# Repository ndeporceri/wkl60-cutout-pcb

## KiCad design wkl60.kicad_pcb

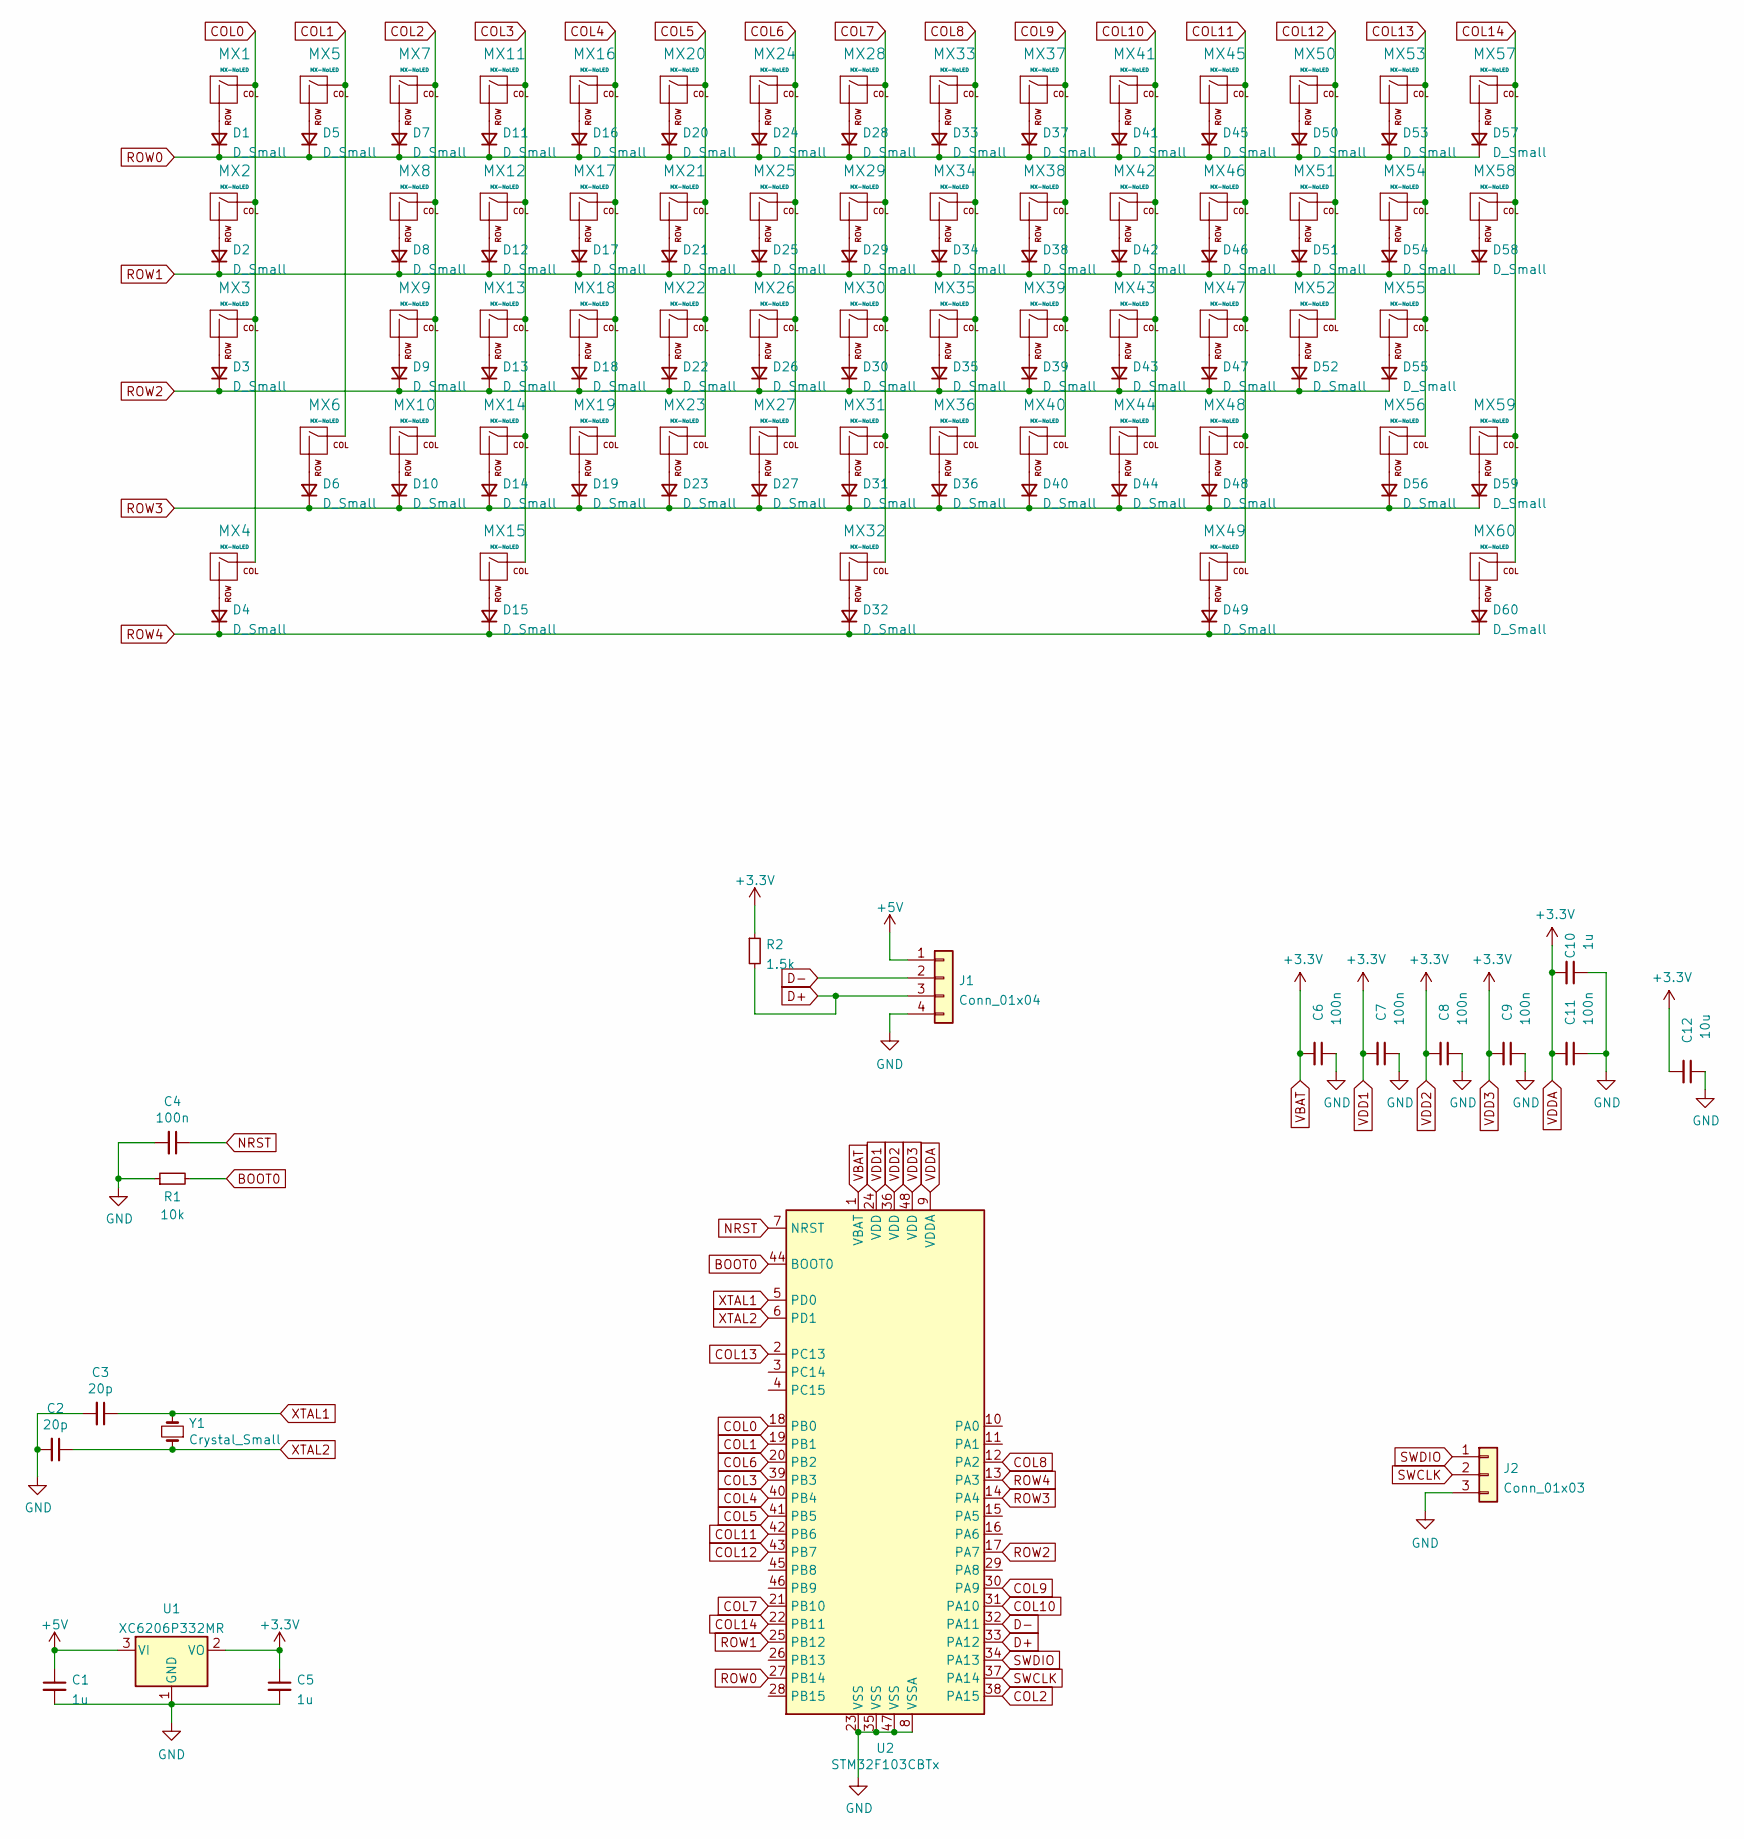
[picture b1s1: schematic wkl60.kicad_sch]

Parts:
C1, C5, C10: 1u; C_0603_1608Metric_Pad1.08x0.95mm_HandSolder
C2, C3: 20p; C_0603_1608Metric_Pad1.08x0.95mm_HandSolder
C4, C6, C7, C8, C9, C11: 100n; C_0603_1608Metric_Pad1.08x0.95mm_HandSolder
C12: 10u; C_0603_1608Metric_Pad1.08x0.95mm_HandSolder
D1, D2, D3, D4, D5, D6, D7, D8, D9, D10, D11, D12, D13, D14, D15, D16, D17, D18, D19, D20, D21, D22, D23, D24, D25, D26, D27, D28, D29, D30, D31, D32, D33, D34, D35, D36, D37, D38, D39, D40, D41, D42, D43, D44, D45, D46, D47, D48, D49, D50, D51, D52, D53, D54, D55, D56, D57, D58, D59, D60: D_Small; D_SOD-123F
J1: Conn_01x04; JST_SH_SM04B-SRSS-TB_1x04-1MP_P1.00mm_Horizontal
J2: Conn_01x03; PinHeader_1x03_P2.54mm_Vertical
MX1, MX5, MX7, MX8, MX9, MX10, MX11, MX12, MX13, MX14, MX16, MX17, MX18, MX19, MX20, MX21, MX22, MX23, MX24, MX25, MX26, MX27, MX28, MX29, MX30, MX31, MX33, MX34, MX35, MX36, MX37, MX38, MX39, MX40, MX41, MX42, MX43, MX44, MX45, MX46, MX47, MX48, MX50, MX51, MX52, MX53, MX54, MX57, MX59: MX-NoLED; MXOnly-1U-NoLED
MX2, MX4, MX15, MX49, MX58, MX60: MX-NoLED; MXOnly-1.5U-NoLED
MX3, MX56: MX-NoLED; MXOnly-1.75U-NoLED
MX6: MX-NoLED; MXOnly-2.25U-ReversedStabilizers-NoLED
MX32: MX-NoLED; MXOnly-7U-ReversedStabilizers-NoLED
MX55: MX-NoLED; MXOnly-2.25U-NoLED
R1: 10k; R_0603_1608Metric_Pad0.98x0.95mm_HandSolder
R2: 1.5k; R_0603_1608Metric_Pad0.98x0.95mm_HandSolder
U1: XC6206P332MR; SOT-23
U2: STM32F103CBTx; LQFP-48_7x7mm_P0.5mm; LCSC C77979
Y1: Crystal_Small; Crystal_SMD_5032-2Pin_5.0x3.2mm; LCSC C115962

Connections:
+5V: C1.1, J1.1, U1.3 (VI)
BOOT0: R1.2, U2.44 (BOOT0)
COL0: MX1.1 (COL), MX2.1 (COL), MX3.1 (COL), MX4.1 (COL), U2.18 (PB0)
COL1: MX5.1 (COL), MX6.1 (COL), U2.19 (PB1)
COL2: MX7.1 (COL), MX8.1 (COL), MX9.1 (COL), MX10.1 (COL), U2.38 (PA15)
COL3: MX11.1 (COL), MX12.1 (COL), MX13.1 (COL), MX14.1 (COL), MX15.1 (COL), U2.39 (PB3)
COL4: MX16.1 (COL), MX17.1 (COL), MX18.1 (COL), MX19.1 (COL), U2.40 (PB4)
COL5: MX20.1 (COL), MX21.1 (COL), MX22.1 (COL), MX23.1 (COL), U2.41 (PB5)
COL6: MX24.1 (COL), MX25.1 (COL), MX26.1 (COL), MX27.1 (COL), U2.20 (PB2)
COL7: MX28.1 (COL), MX29.1 (COL), MX30.1 (COL), MX31.1 (COL), MX32.1 (COL), U2.21 (PB10)
COL8: MX33.1 (COL), MX34.1 (COL), MX35.1 (COL), MX36.1 (COL), U2.12 (PA2)
COL9: MX37.1 (COL), MX38.1 (COL), MX39.1 (COL), MX40.1 (COL), U2.30 (PA9)
COL10: MX41.1 (COL), MX42.1 (COL), MX43.1 (COL), MX44.1 (COL), U2.31 (PA10)
COL11: MX45.1 (COL), MX46.1 (COL), MX47.1 (COL), MX48.1 (COL), MX49.1 (COL), U2.42 (PB6)
COL12: MX50.1 (COL), MX51.1 (COL), MX52.1 (COL), U2.43 (PB7)
COL13: MX53.1 (COL), MX54.1 (COL), MX55.1 (COL), MX56.1 (COL), U2.2 (PC13)
COL14: MX57.1 (COL), MX58.1 (COL), MX59.1 (COL), MX60.1 (COL), U2.22 (PB11)
D+: J1.3, R2.2, U2.33 (PA12)
D-: J1.2, U2.32 (PA11)
GND: C1.2, C2.2, C3.2, C4.2, C5.2, C6.1, C7.1, C8.1, C9.1, C10.1, C11.1, C12.1, J1.4, J2.3, R1.1, U1.1 (GND), U2.8 (VSSA), U2.23 (VSS), U2.35 (VSS), U2.47 (VSS)
NRST: C4.1, U2.7 (NRST)
unnamed: D1.2 (A), MX1.2 (ROW)
unnamed: D2.2 (A), MX2.2 (ROW)
unnamed: D3.2 (A), MX3.2 (ROW)
unnamed: D4.2 (A), MX4.2 (ROW)
unnamed: D5.2 (A), MX5.2 (ROW)
unnamed: D6.2 (A), MX6.2 (ROW)
unnamed: D7.2 (A), MX7.2 (ROW)
unnamed: D8.2 (A), MX8.2 (ROW)
unnamed: D9.2 (A), MX9.2 (ROW)
unnamed: D10.2 (A), MX10.2 (ROW)
unnamed: D11.2 (A), MX11.2 (ROW)
unnamed: D12.2 (A), MX12.2 (ROW)
unnamed: D13.2 (A), MX13.2 (ROW)
unnamed: D14.2 (A), MX14.2 (ROW)
unnamed: D15.2 (A), MX15.2 (ROW)
unnamed: D16.2 (A), MX16.2 (ROW)
unnamed: D17.2 (A), MX17.2 (ROW)
unnamed: D18.2 (A), MX18.2 (ROW)
unnamed: D19.2 (A), MX19.2 (ROW)
unnamed: D20.2 (A), MX20.2 (ROW)
unnamed: D21.2 (A), MX21.2 (ROW)
unnamed: D22.2 (A), MX22.2 (ROW)
unnamed: D23.2 (A), MX23.2 (ROW)
unnamed: D24.2 (A), MX24.2 (ROW)
unnamed: D25.2 (A), MX25.2 (ROW)
unnamed: D26.2 (A), MX26.2 (ROW)
unnamed: D27.2 (A), MX27.2 (ROW)
unnamed: D28.2 (A), MX28.2 (ROW)
unnamed: D29.2 (A), MX29.2 (ROW)
unnamed: D30.2 (A), MX30.2 (ROW)
unnamed: D31.2 (A), MX31.2 (ROW)
unnamed: D32.2 (A), MX32.2 (ROW)
unnamed: D33.2 (A), MX33.2 (ROW)
unnamed: D34.2 (A), MX34.2 (ROW)
unnamed: D35.2 (A), MX35.2 (ROW)
unnamed: D36.2 (A), MX36.2 (ROW)
unnamed: D37.2 (A), MX37.2 (ROW)
unnamed: D38.2 (A), MX38.2 (ROW)
unnamed: D39.2 (A), MX39.2 (ROW)
unnamed: D40.2 (A), MX40.2 (ROW)
unnamed: D41.2 (A), MX41.2 (ROW)
unnamed: D42.2 (A), MX42.2 (ROW)
unnamed: D43.2 (A), MX43.2 (ROW)
unnamed: D44.2 (A), MX44.2 (ROW)
unnamed: D45.2 (A), MX45.2 (ROW)
unnamed: D46.2 (A), MX46.2 (ROW)
unnamed: D47.2 (A), MX47.2 (ROW)
unnamed: D48.2 (A), MX48.2 (ROW)
unnamed: D49.2 (A), MX49.2 (ROW)
unnamed: D50.2 (A), MX50.2 (ROW)
unnamed: D51.2 (A), MX51.2 (ROW)
unnamed: D52.2 (A), MX52.2 (ROW)
unnamed: D53.2 (A), MX53.2 (ROW)
unnamed: D54.2 (A), MX54.2 (ROW)
unnamed: D55.2 (A), MX55.2 (ROW)
unnamed: D56.2 (A), MX56.2 (ROW)
unnamed: D57.2 (A), MX57.2 (ROW)
unnamed: D58.2 (A), MX58.2 (ROW)
unnamed: D59.2 (A), MX59.2 (ROW)
unnamed: D60.2 (A), MX60.2 (ROW)
ROW0: D1.1 (K), D5.1 (K), D7.1 (K), D11.1 (K), D16.1 (K), D20.1 (K), D24.1 (K), D28.1 (K), D33.1 (K), D37.1 (K), D41.1 (K), D45.1 (K), D50.1 (K), D53.1 (K), D57.1 (K), U2.27 (PB14)
ROW1: D2.1 (K), D8.1 (K), D12.1 (K), D17.1 (K), D21.1 (K), D25.1 (K), D29.1 (K), D34.1 (K), D38.1 (K), D42.1 (K), D46.1 (K), D51.1 (K), D54.1 (K), D58.1 (K), U2.25 (PB12)
ROW2: D3.1 (K), D9.1 (K), D13.1 (K), D18.1 (K), D22.1 (K), D26.1 (K), D30.1 (K), D35.1 (K), D39.1 (K), D43.1 (K), D47.1 (K), D52.1 (K), D55.1 (K), U2.17 (PA7)
ROW3: D6.1 (K), D10.1 (K), D14.1 (K), D19.1 (K), D23.1 (K), D27.1 (K), D31.1 (K), D36.1 (K), D40.1 (K), D44.1 (K), D48.1 (K), D56.1 (K), D59.1 (K), U2.14 (PA4)
ROW4: D4.1 (K), D15.1 (K), D32.1 (K), D49.1 (K), D60.1 (K), U2.13 (PA3)
SWCLK: J2.2, U2.37 (PA14)
SWDIO: J2.1, U2.34 (PA13)
VBAT: C5.1, C6.2, C7.2, C8.2, C9.2, C10.2, C11.2, C12.2, R2.1, U1.2 (VO), U2.1 (VBAT), U2.9 (VDDA), U2.24 (VDD), U2.36 (VDD), U2.48 (VDD)
XTAL1: C3.1, U2.5 (PD0), Y1.2
XTAL2: C2.1, U2.6 (PD1), Y1.1

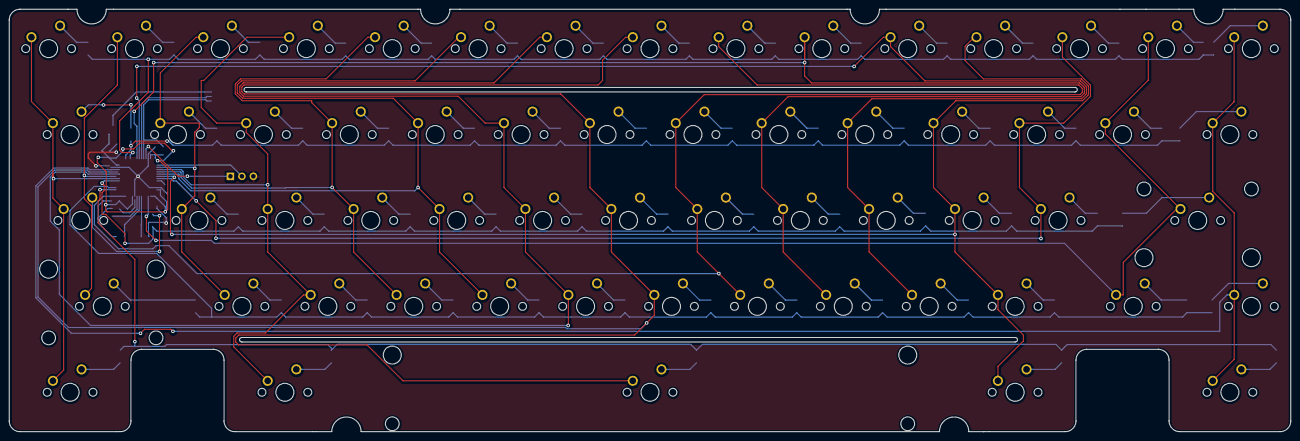
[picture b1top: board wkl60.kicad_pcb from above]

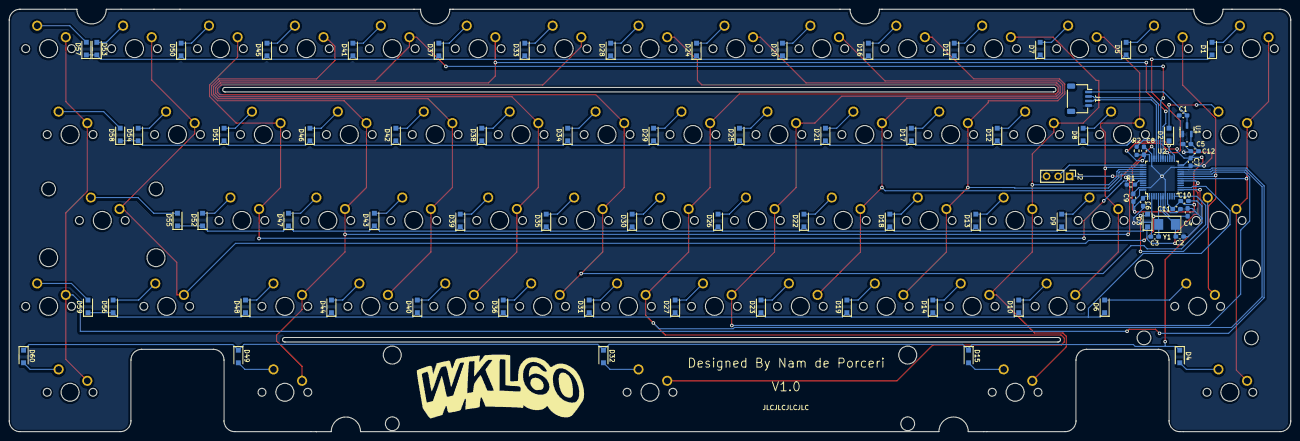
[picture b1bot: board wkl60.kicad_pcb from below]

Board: 2 copper layers, 284.2 x 93.7 mm, 139 parts (79 on the bottom side), 91 nets.

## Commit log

2023-06-08 uploaded kicad project folder
